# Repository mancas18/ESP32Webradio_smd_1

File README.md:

# ESP32Webradio_smd

Idee von https://www.az-delivery.de/blogs/azdelivery-blog-fur-arduino-und-raspberry-pi/internet-radio-mit-dem-esp32

2 Elkos an die ESP-Ausgänge, der Verstärker entfällt um Aktivboxen anzuschließen

OLED Display statt LCD

smd Bestückung

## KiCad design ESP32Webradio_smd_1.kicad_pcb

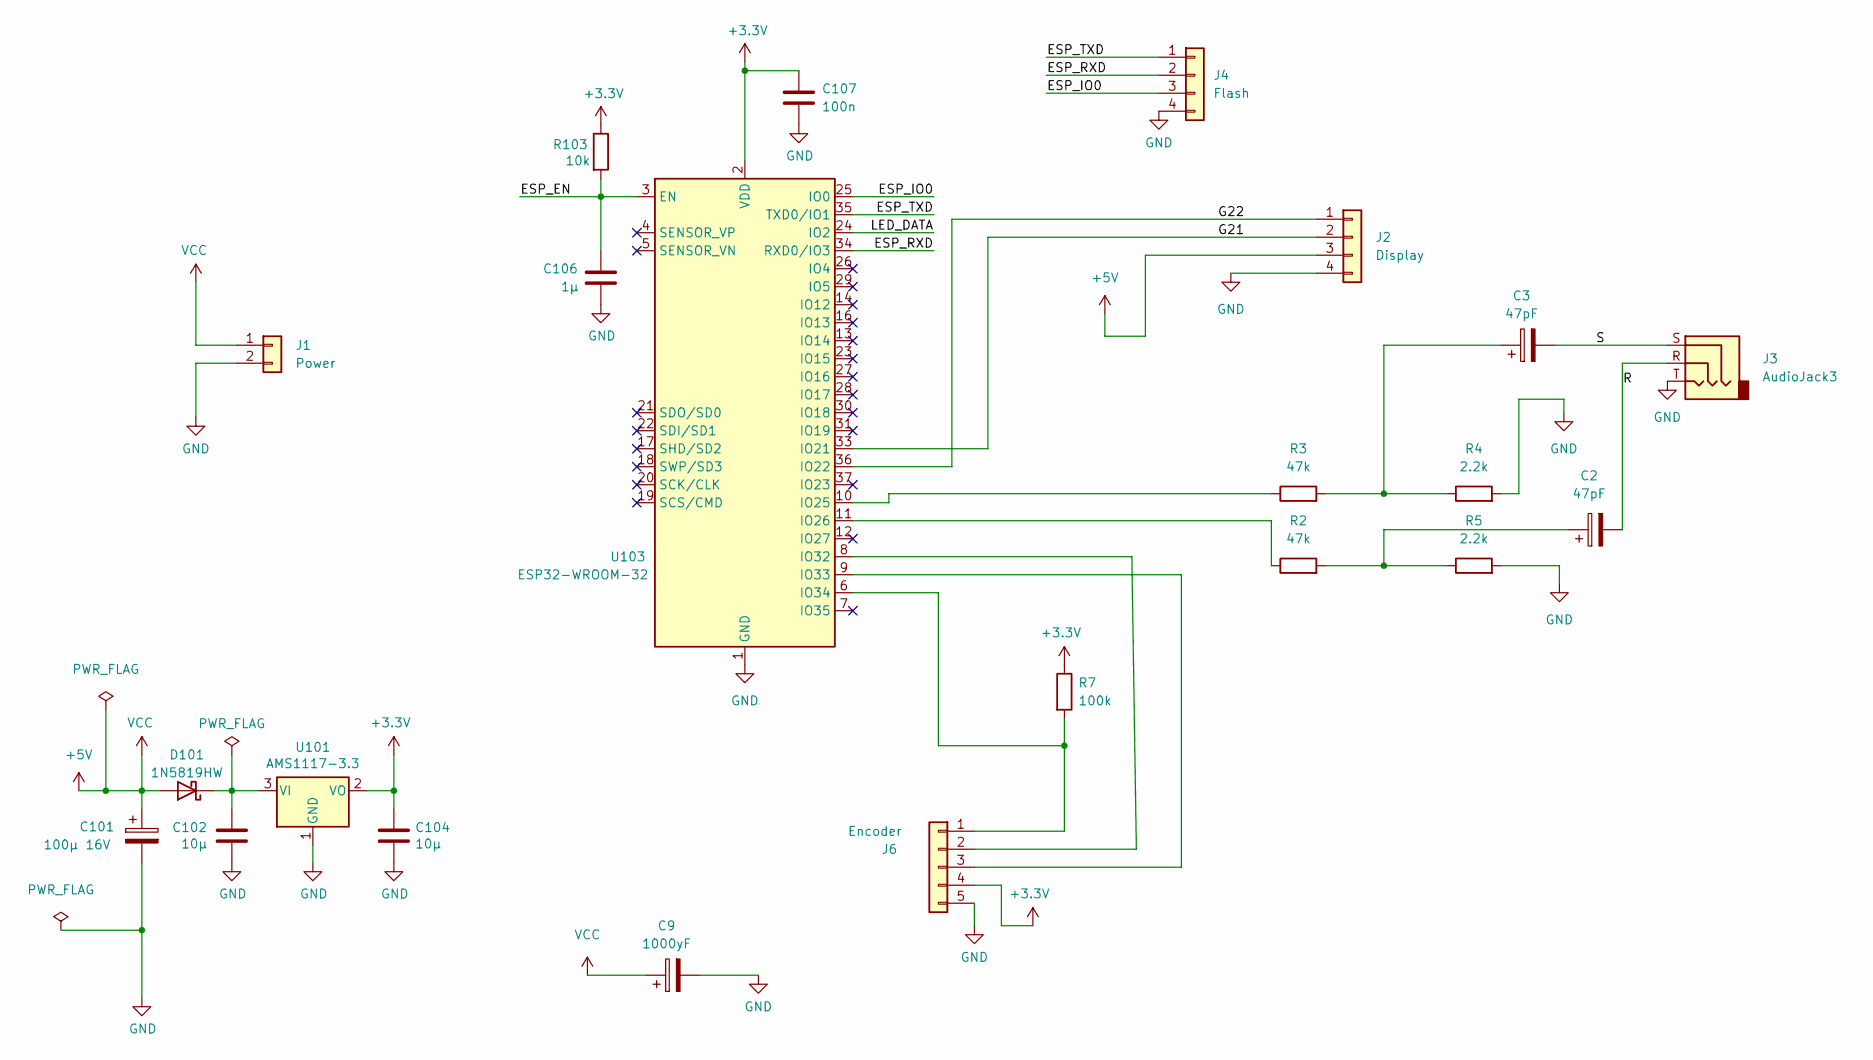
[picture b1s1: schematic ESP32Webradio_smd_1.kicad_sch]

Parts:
C2, C3: 47pF; CP_Radial_D4.0mm_P2.00mm
C9: 1000yF; CP_Radial_D10.0mm_P2.50mm
C101: 100µ 16V; CP_Elec_6.3x5.4
C102, C104: 10µ; C_0603_1608Metric
C106: 1µ; C_0603_1608Metric
C107: 100n; C_0603_1608Metric
D101: 1N5819HW; D_SOD-123
J1: Power; PinHeader_1x02_P2.54mm_Vertical
J2: Display; PinHeader_1x04_P2.54mm_Vertical
J3: AudioJack3; AudioJack
J4: Flash; PinHeader_1x04_P2.54mm_Vertical
J6: Encoder; PinHeader_1x05_P2.54mm_Vertical
R2, R3: 47k; R_Axial_DIN0309_L9.0mm_D3.2mm_P2.54mm_Vertical
R4, R5: 2.2k; R_Axial_DIN0309_L9.0mm_D3.2mm_P2.54mm_Vertical
R7: 100k; R_Axial_DIN0309_L9.0mm_D3.2mm_P2.54mm_Vertical
R103: 10k; R_0603_1608Metric
U101: AMS1117-3.3; SOT-223-3_TabPin2
U103: ESP32-WROOM-32

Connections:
+3V3: C104.1, C107.1, J6.4, R7.1, R103.1, U101.2 (VO), U103.2 (VDD)
+5V: C9.1, C101.1, D101.2 (A), J1.1, J2.3
/ESP_EN: C106.1, R103.2, U103.3 (EN)
/ESP_IO0: J4.3, U103.25 (IO0)
/ESP_RXD: J4.2, U103.34 (RXD0/IO3)
/ESP_TXD: J4.1, U103.35 (TXD0/IO1)
/G21: J2.2, U103.33 (IO21)
/G22: J2.1, U103.36 (IO22)
/LED_DATA: U103.24 (IO2)
/R: C2.2, J3.R
/S: C3.2, J3.S
GND: C9.2, C101.2, C102.2, C104.2, C106.2, C107.2, J1.2, J2.4, J3.T, J4.4, J6.5, R4.2, R5.2, U101.1 (GND), U103.1 (GND), U103.15 (GND), U103.38 (GND), U103.39 (GND)
unnamed: C2.1, R2.2, R5.1
unnamed: C3.1, R3.2, R4.1
unnamed: C102.1, D101.1 (K), U101.3 (VI)
unnamed: J6.1, R7.2, U103.6 (IO34)
unnamed: J6.2, U103.8 (IO32)
unnamed: J6.3, U103.9 (IO33)
unnamed: R2.1, U103.11 (IO26)
unnamed: R3.1, U103.10 (IO25)

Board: 2 copper layers, 22 parts (0 on the bottom side), 19 nets, no tracks yet.

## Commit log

2022-05-31 initial upload
2022-06-02 new implementation with encoder
2022-06-02 with usb plug
2022-06-02 DimensionSketch
2022-06-06 KiCad Projekt
